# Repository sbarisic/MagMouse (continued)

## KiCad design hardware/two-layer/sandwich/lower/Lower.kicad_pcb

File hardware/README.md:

# Electronics

The [active three-board design](two-layer/sandwich/README.md) uses two copper
layers on each board, passive plastic button clicks and Hall sensing.
Lower and Upper are 70 x 100 mm; Wheel is 70 x 67 mm
with chamfered top corners. All three have independent schematics and routing.

- [Editable projects and reviews](two-layer/sandwich/README.md)
- [Manufacturing quote package](two-layer/sandwich/quote-package/README.md)
- [Combined panel](two-layer/sandwich/panel/Panel.kicad_pcb)
- [3D models](two-layer/sandwich/3d/README.md)
- [Shared libraries and helpers](common/README.md)
- [Historical brake simulation](simulation/brake/README.md)
- [Previous revisions in Git](../docs/history/README.md)

Mechanical integration, supplier acceptance, firmware and physical electronics
qualification remain open. The legacy BOM and circuit/layout notes outside the
active projects contain historical material; use the active schematics and
quote-package BOM for the current fitted components.

License: CERN-OHL-S-2.0; see [LICENSE](LICENSE).
Source location: <https://github.com/sbarisic/MagMouse>.

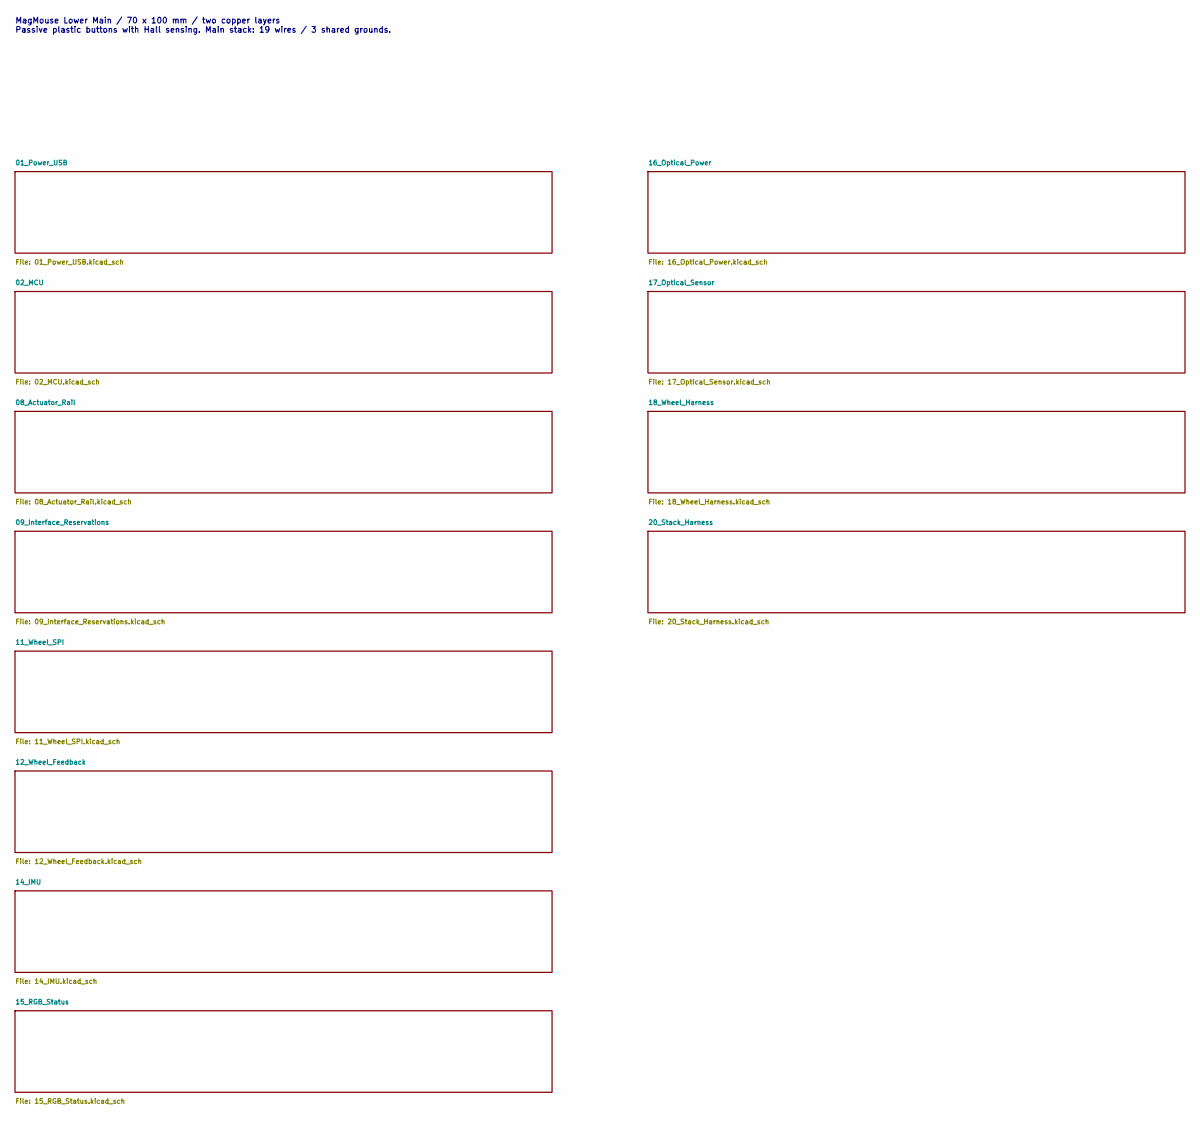
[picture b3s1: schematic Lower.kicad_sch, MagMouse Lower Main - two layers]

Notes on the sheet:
MagMouse Lower Main / 70 x 100 mm / two copper layers Passive plastic buttons with Hall sensing. Main stack: 19 wires / 3 shared grounds.

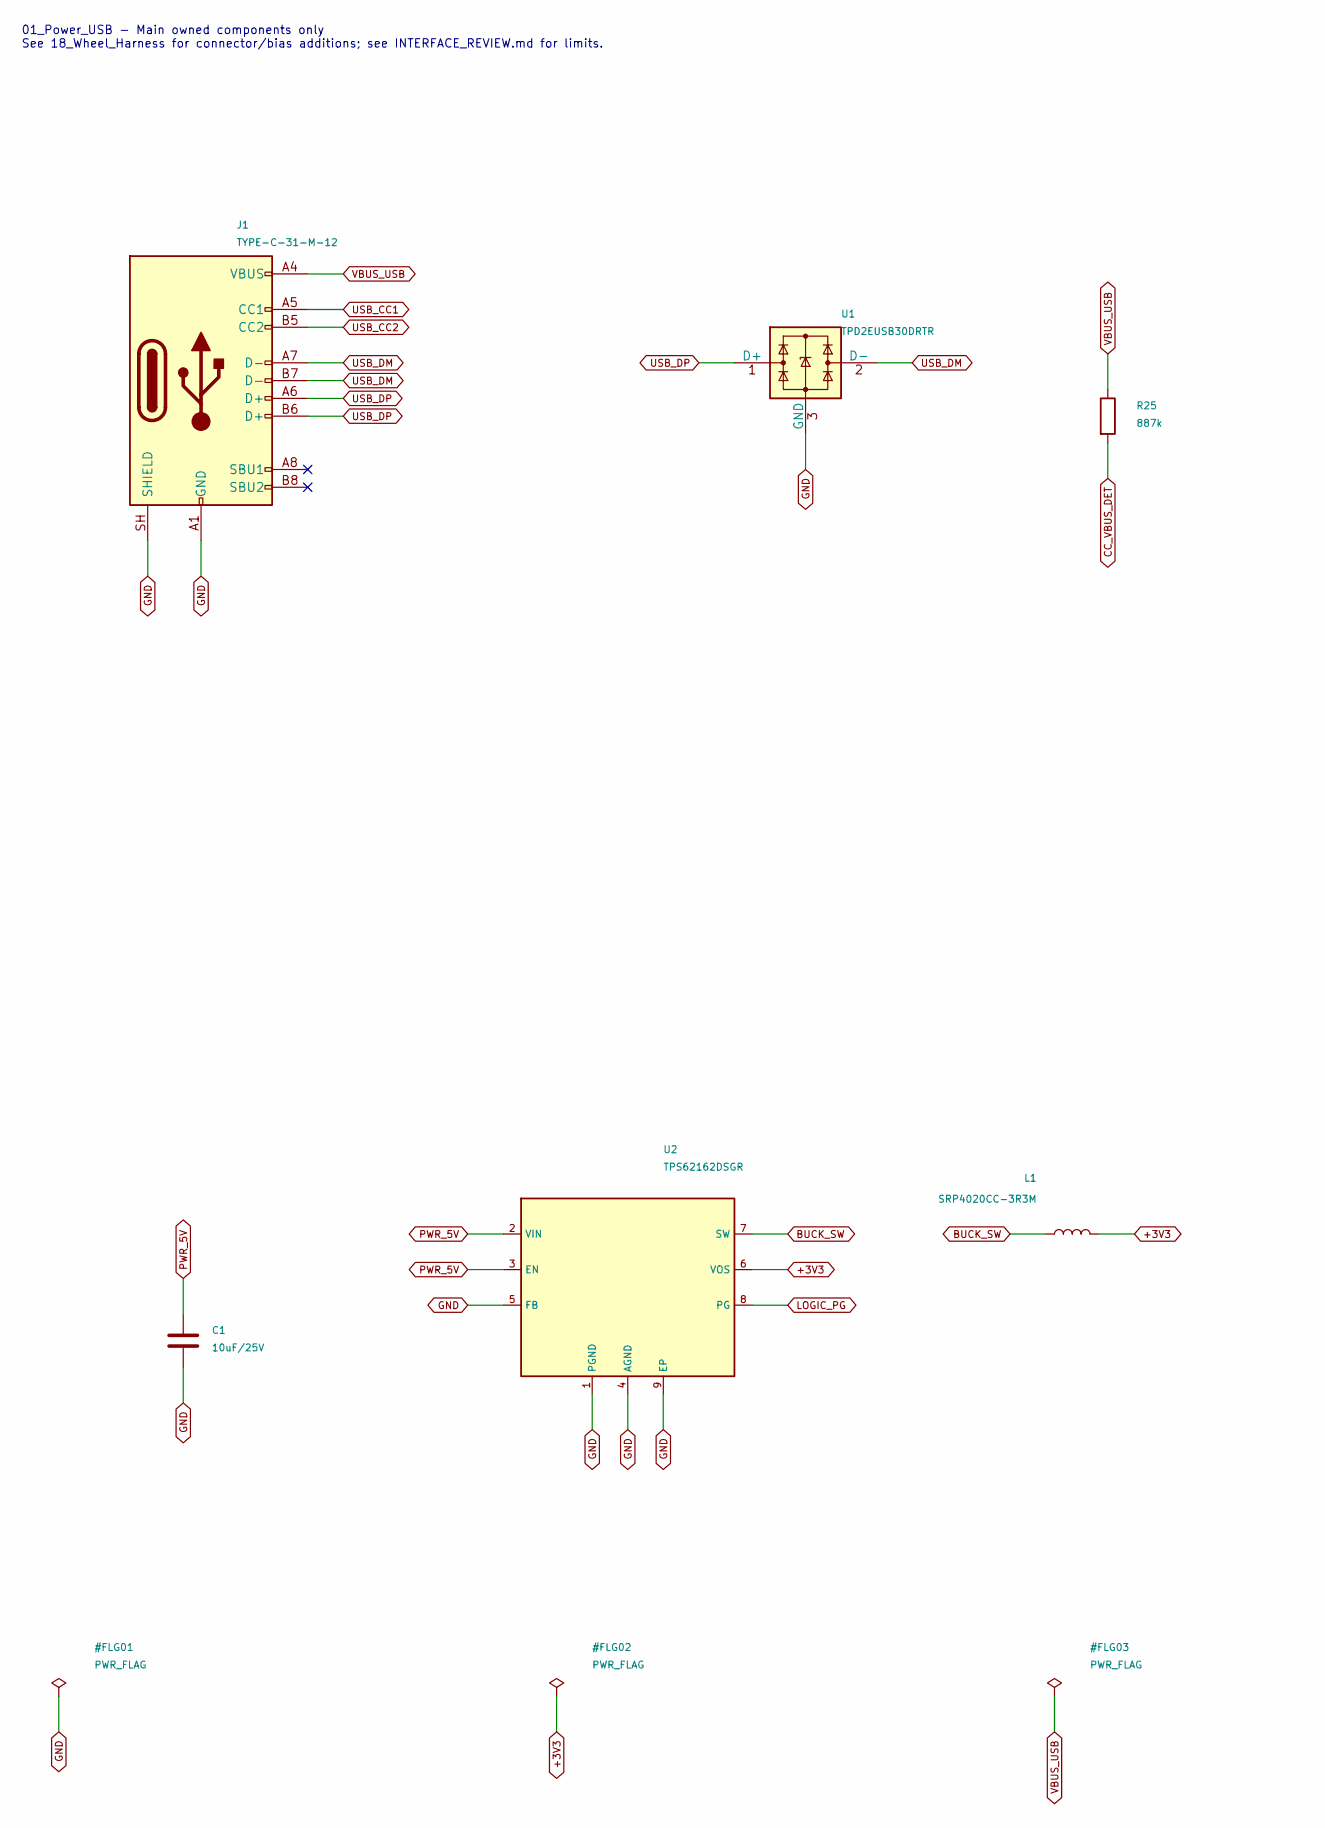
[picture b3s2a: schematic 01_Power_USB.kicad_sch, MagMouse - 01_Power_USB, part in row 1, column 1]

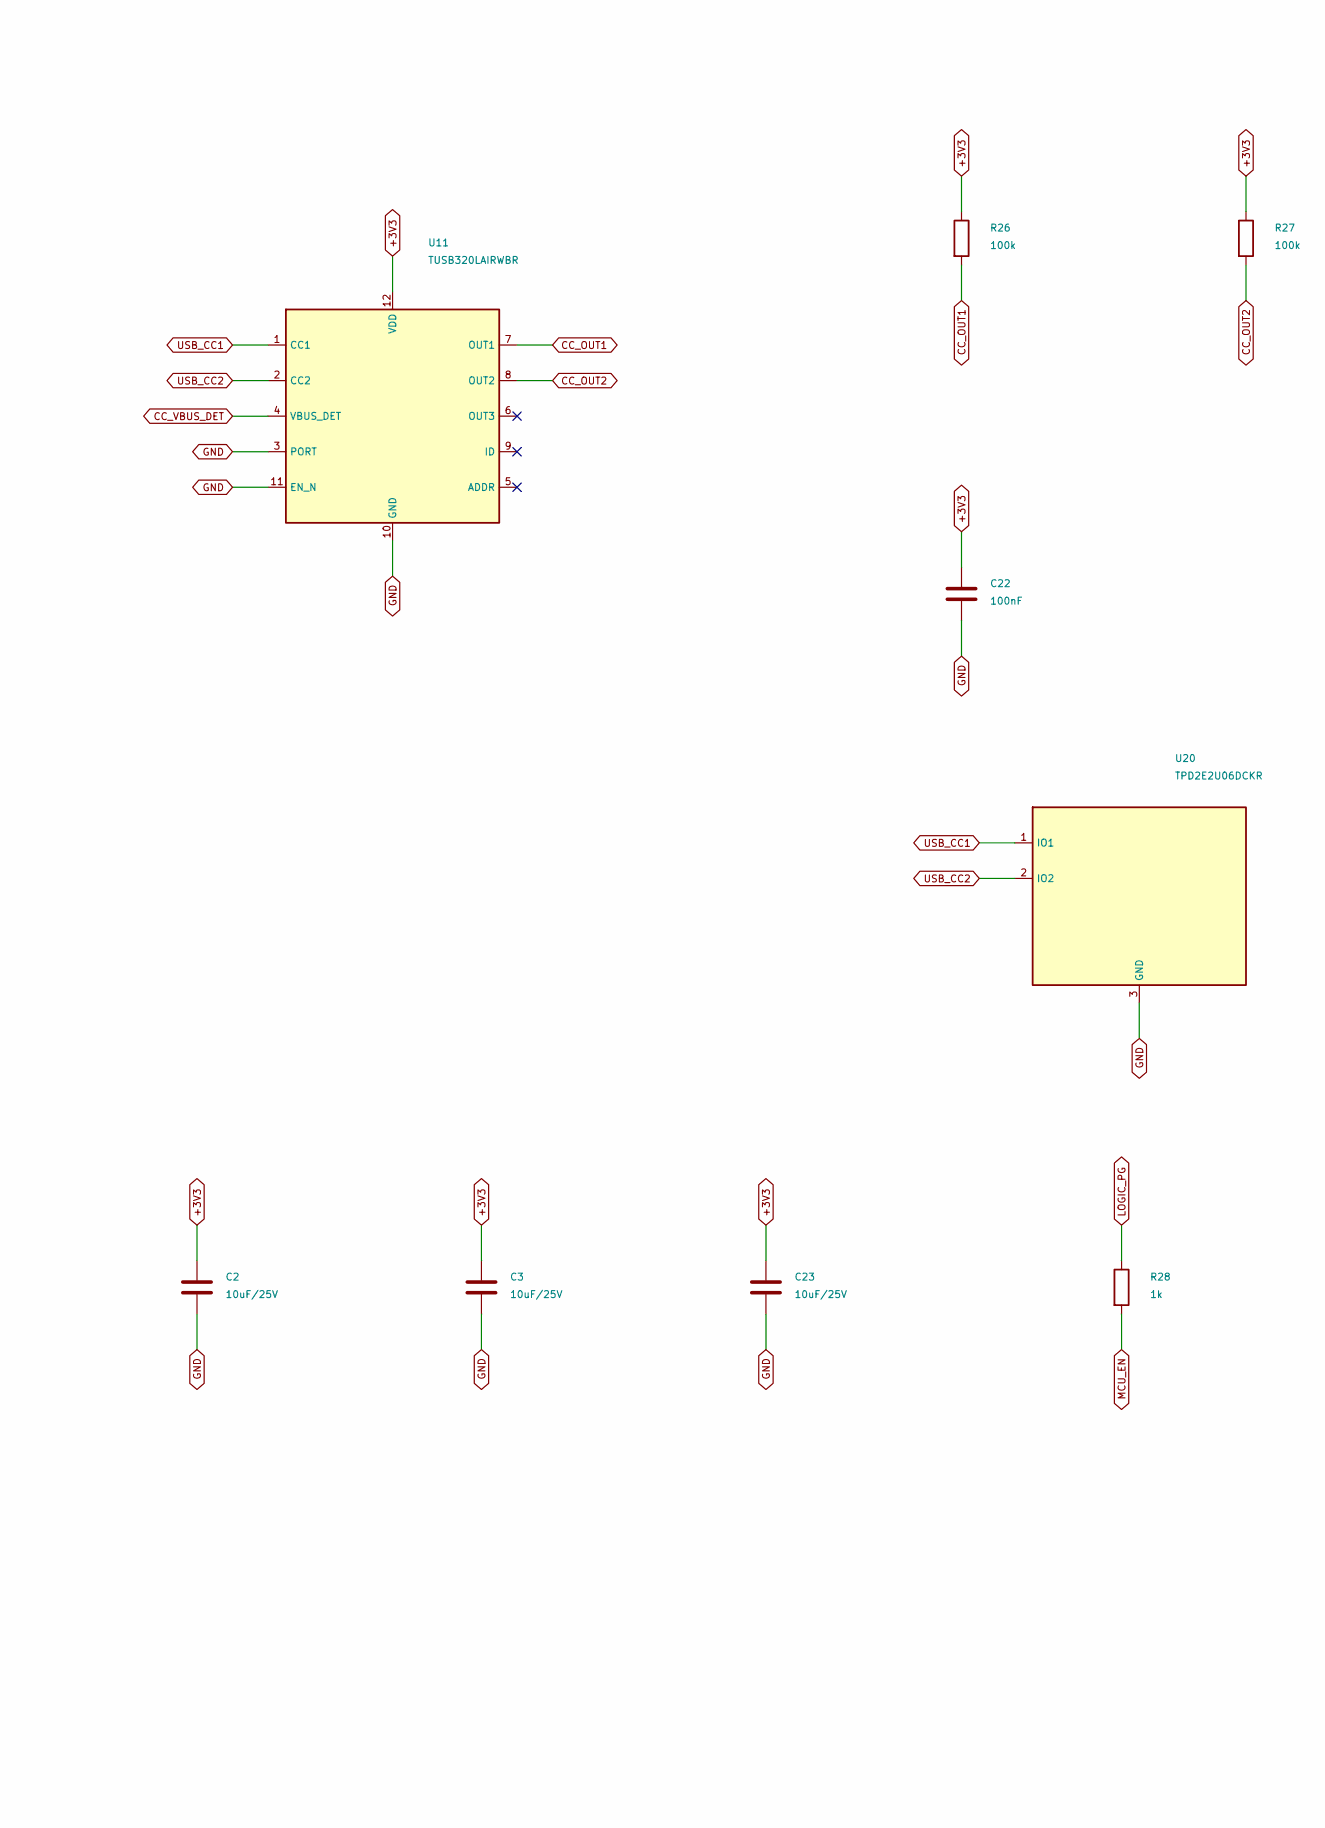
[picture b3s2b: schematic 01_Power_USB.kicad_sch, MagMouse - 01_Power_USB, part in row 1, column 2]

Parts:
C1, C2, C3, C23: 10uF/25V; C_1206_3216Metric; Rating 25 V, X5R, 10%; MPN CL31A106KAHNNNE
C22: 100nF; C_1206_3216Metric; Rating 50 V, X7R, 10%; MPN CC1206KRX7R9BB104
J1: TYPE-C-31-M-12; USB_C_Receptacle_HRO_TYPE-C-31-M-12; MPN TYPE-C-31-M-12; LCSC C165948
L1: SRP4020CC-3R3M; L_Bourns_SRP4020CC; MPN SRP4020CC-3R3M
R25: 887k; R_1206_3216Metric; Rating 0.25 W, 1%; MPN RC1206FR-07887KL
R26, R27: 100k; R_1206_3216Metric; Rating 0.25 W, 1%; MPN RC1206FR-07100KL
R28: 1k; R_1206_3216Metric; Rating 0.25 W, 1%; MPN RC1206FR-071KL
U1: TPD2EUSB30DRTR; Texas_DRT-3; MPN TPD2EUSB30DRTR; LCSC C97502
U2: TPS62162DSGR; Texas_DSG0008A_WSON-8-1EP_2x2mm_P0.5mm_EP0.9x1.6mm; MPN TPS62162DSGR; LCSC C40256
U11: TUSB320LAIRWBR; Texas_X2QFN-12_1.6x1.6mm_P0.4mm; MPN TUSB320LAIRWBR; LCSC C132554
U20: TPD2E2U06DCKR; SOT-323_SC-70; MPN TPD2E2U06DCKR; LCSC C1855726

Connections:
+3V3: C2.1, C3.1, C22.1, C23.1, L1.2, R26.1, R27.1, U2.6 (VOS), U11.12 (VDD); also elsewhere on the board
BUCK_SW: L1.1, U2.7 (SW)
CC_OUT1: R26.2, U11.7 (OUT1); also elsewhere on the board
CC_OUT2: R27.2, U11.8 (OUT2); also elsewhere on the board
CC_VBUS_DET: R25.2, U11.4 (VBUS_DET)
GND: C1.2, C2.2, C3.2, C22.2, C23.2, J1.A1 (GND), J1.A12 (GND), J1.B1 (GND), J1.B12 (GND), J1.SH (SHIELD), U1.3 (GND), U2.1 (PGND), U2.4 (AGND), U2.5 (FB), U2.9 (EP), U11.3 (PORT), U11.10 (GND), U11.11 (EN_N), U20.3 (GND); also elsewhere on the board
LOGIC_PG: R28.1, U2.8 (PG)
MCU_EN: R28.2; also elsewhere on the board
PWR_5V: C1.1, U2.2 (VIN), U2.3 (EN); also elsewhere on the board
USB_CC1: J1.A5 (CC1), U11.1 (CC1), U20.1 (IO1)
USB_CC2: J1.B5 (CC2), U11.2 (CC2), U20.2 (IO2)
USB_DM: J1.A7 (D-), J1.B7 (D-), U1.2 (D-); also elsewhere on the board
USB_DP: J1.A6 (D+), J1.B6 (D+), U1.1 (D+); also elsewhere on the board
VBUS_USB: J1.A4 (VBUS), J1.A9 (VBUS), J1.B4 (VBUS), J1.B9 (VBUS), R25.1; also elsewhere on the board

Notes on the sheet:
01_Power_USB - Main owned components only See 18_Wheel_Harness for connector/bias additions; see INTERFACE_REVIEW.md for limits.

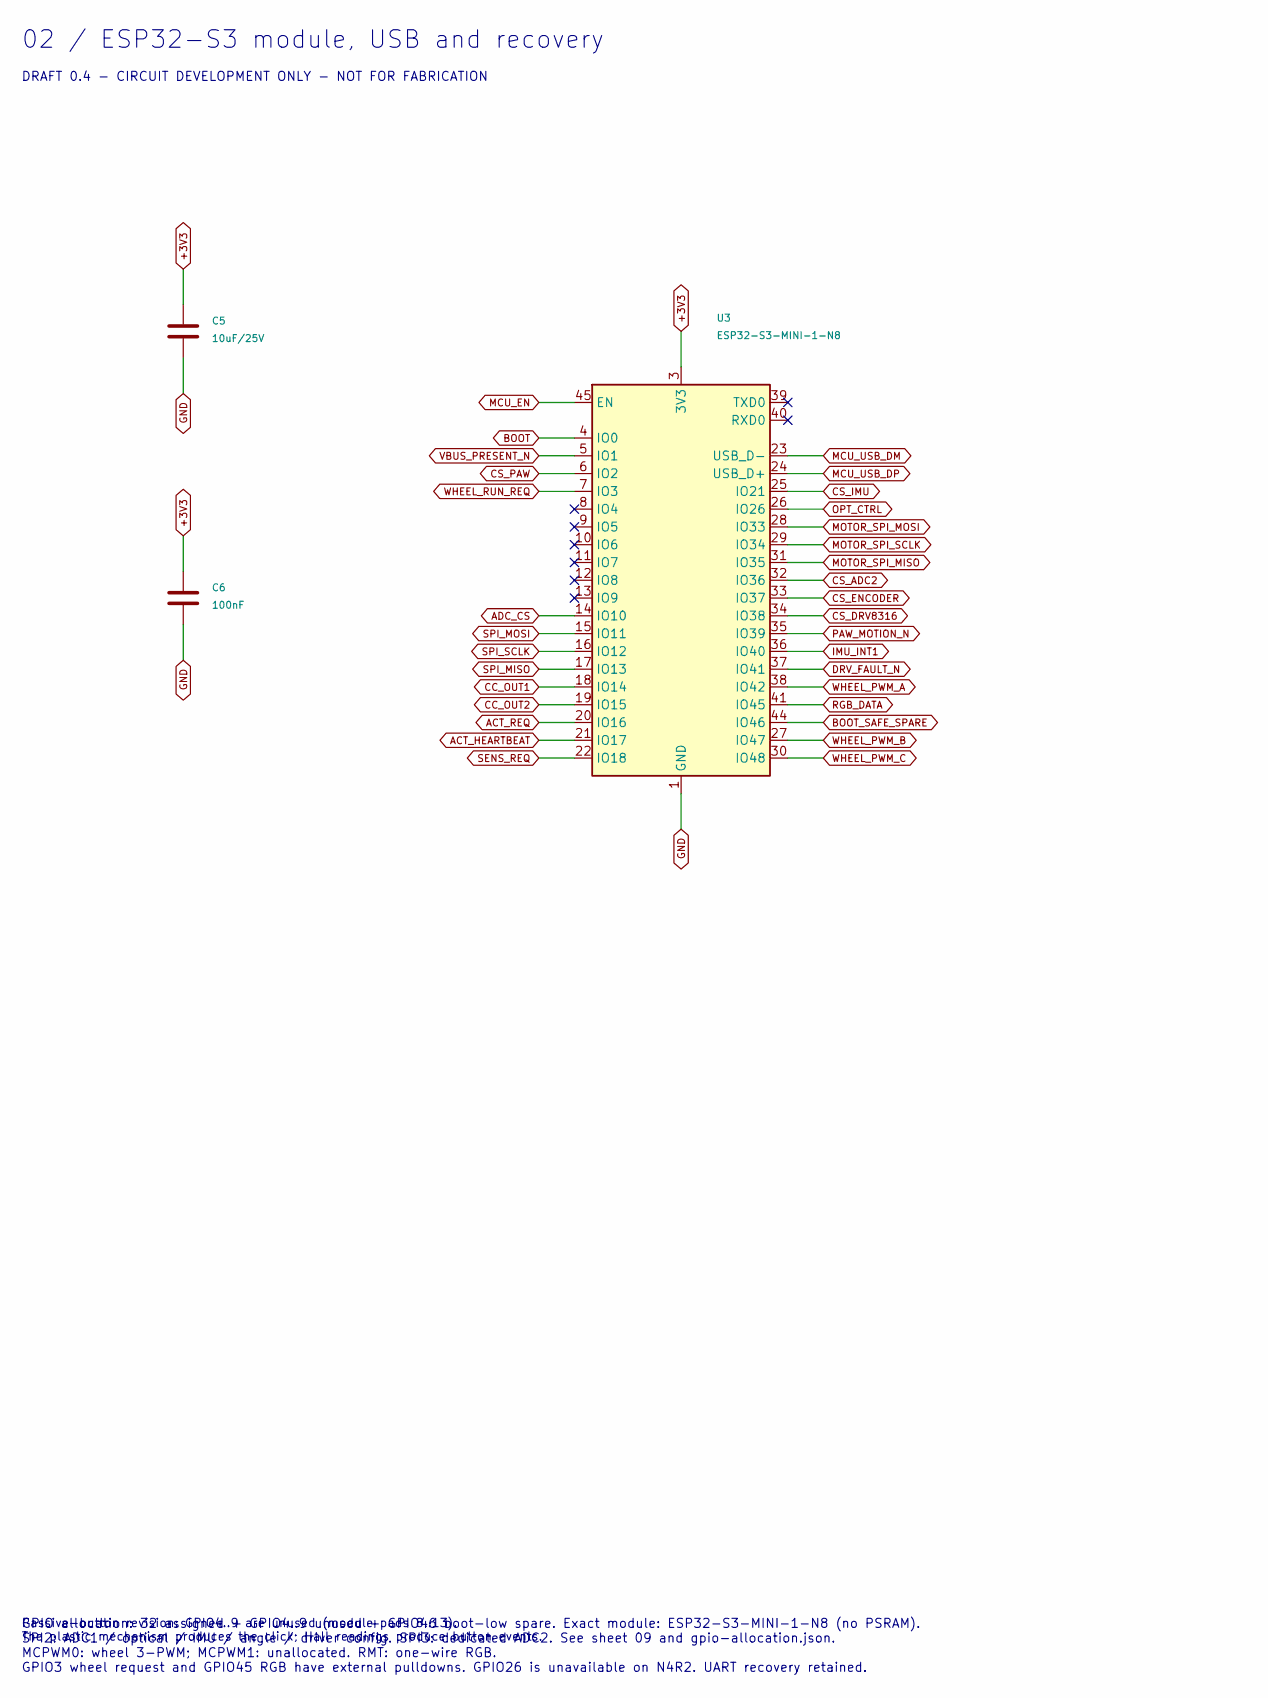
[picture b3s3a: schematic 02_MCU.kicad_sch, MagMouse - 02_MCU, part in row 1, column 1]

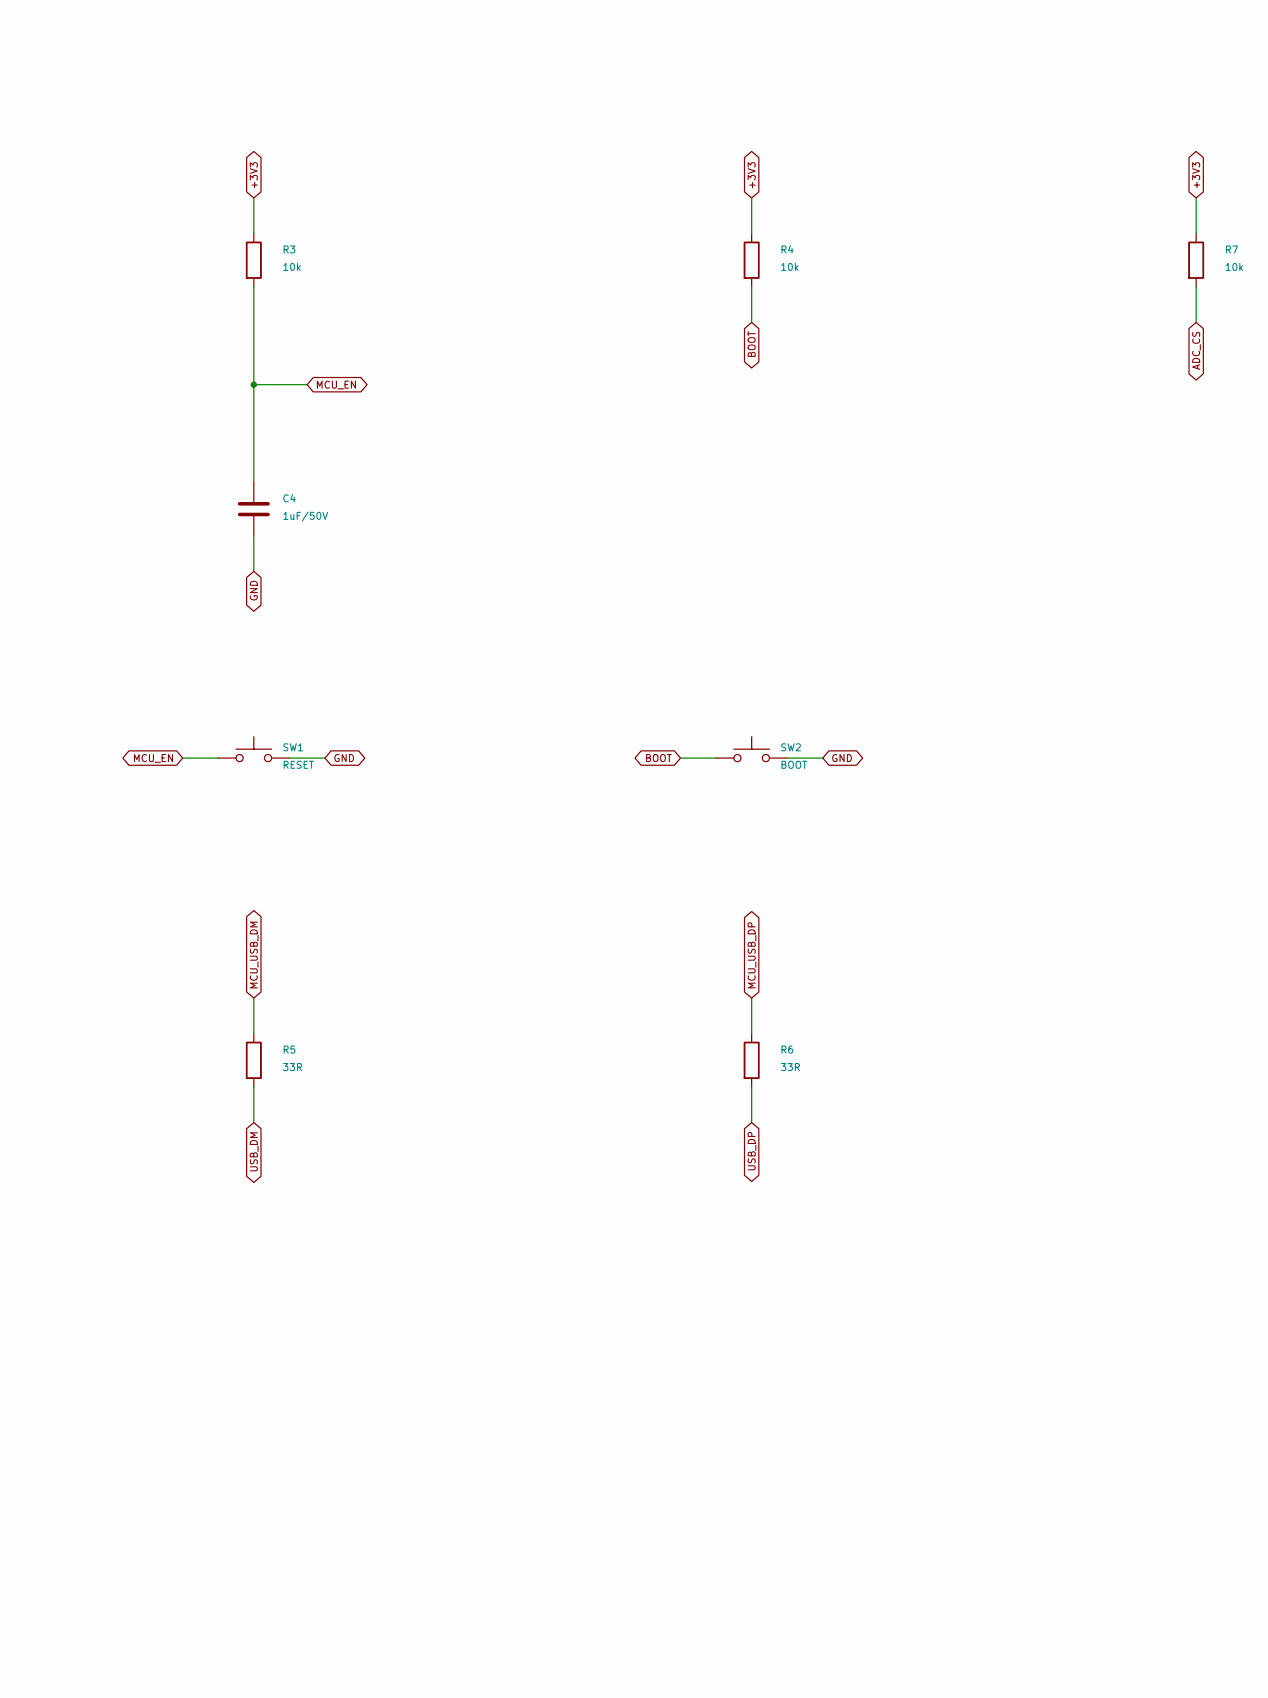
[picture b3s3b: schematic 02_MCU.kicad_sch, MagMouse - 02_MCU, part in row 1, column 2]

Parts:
C4: 1uF/50V; C_1206_3216Metric; Rating 50 V, X7R, 10%; MPN CL31B105KBHNNNE; JLCPCB Library Type Basic
C5: 10uF/25V; C_1206_3216Metric; Rating 25 V, X5R, 10%; MPN CL31A106KAHNNNE
C6: 100nF; C_1206_3216Metric; Rating 50 V, X7R, 10%; MPN CC1206KRX7R9BB104
R3, R4, R7: 10k; R_1206_3216Metric; Rating 0.25 W, 1%; MPN RC1206FR-0710KL
R5, R6: 33R; R_1206_3216Metric; Rating 0.25 W, 1%; MPN RC1206FR-0733RL
SW1: RESET; SW_SPST_TS-1088-xR020; MPN TS-1088-AR02016; LCSC C720477
SW2: BOOT; SW_SPST_TS-1088-xR020; MPN TS-1088-AR02016; LCSC C720477
U3: ESP32-S3-MINI-1-N8; ESP32-S2-MINI-1; MPN ESP32-S3-MINI-1-N8; LCSC C2913206

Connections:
+3V3: C5.1, C6.1, R3.1, R4.1, R7.1, U3.3 (3V3); also elsewhere on the board
ACT_HEARTBEAT: U3.21 (IO17); also elsewhere on the board
ACT_REQ: U3.20 (IO16); also elsewhere on the board
ADC_CS: R7.2, U3.14 (IO10); also elsewhere on the board
BOOT: R4.2, SW2.1, U3.4 (IO0)
BOOT_SAFE_SPARE: U3.44 (IO46); also elsewhere on the board
CC_OUT1: U3.18 (IO14); also elsewhere on the board
CC_OUT2: U3.19 (IO15); also elsewhere on the board
CS_ADC2: U3.32 (IO36); also elsewhere on the board
CS_DRV8316: U3.34 (IO38); also elsewhere on the board
CS_ENCODER: U3.33 (IO37); also elsewhere on the board
CS_IMU: U3.25 (IO21); also elsewhere on the board
CS_PAW: U3.6 (IO2); also elsewhere on the board
DRV_FAULT_N: U3.37 (IO41); also elsewhere on the board
GND: C4.2, C5.2, C6.2, SW1.2, SW2.2, U3.1 (GND), U3.2 (GND), U3.42 (GND), U3.43 (GND), U3.46 (GND), U3.47 (GND), U3.48 (GND), U3.49 (GND), U3.50 (GND), U3.51 (GND), U3.52 (GND), U3.53 (GND), U3.54 (GND), U3.55 (GND), U3.56 (GND), U3.57 (GND), U3.58 (GND), U3.59 (GND), U3.60 (GND), U3.61 (GND), U3.62 (GND), U3.63 (GND), U3.64 (GND), U3.65 (GND); also elsewhere on the board
IMU_INT1: U3.36 (IO40); also elsewhere on the board
MCU_EN: C4.1, R3.2, SW1.1, U3.45 (EN); also elsewhere on the board
MCU_USB_DM: R5.1, U3.23 (USB_D-)
MCU_USB_DP: R6.1, U3.24 (USB_D+)
MOTOR_SPI_MISO: U3.31 (IO35); also elsewhere on the board
MOTOR_SPI_MOSI: U3.28 (IO33); also elsewhere on the board
MOTOR_SPI_SCLK: U3.29 (IO34); also elsewhere on the board
OPT_CTRL: U3.26 (IO26); also elsewhere on the board
PAW_MOTION_N: U3.35 (IO39); also elsewhere on the board
RGB_DATA: U3.41 (IO45); also elsewhere on the board
SENS_REQ: U3.22 (IO18); also elsewhere on the board
SPI_MISO: U3.17 (IO13); also elsewhere on the board
SPI_MOSI: U3.15 (IO11); also elsewhere on the board
SPI_SCLK: U3.16 (IO12); also elsewhere on the board
USB_DM: R5.2; also elsewhere on the board
USB_DP: R6.2; also elsewhere on the board
VBUS_PRESENT_N: U3.5 (IO1); also elsewhere on the board
WHEEL_PWM_A: U3.38 (IO42); also elsewhere on the board
WHEEL_PWM_B: U3.27 (IO47); also elsewhere on the board
WHEEL_PWM_C: U3.30 (IO48); also elsewhere on the board
WHEEL_RUN_REQ: U3.7 (IO3); also elsewhere on the board

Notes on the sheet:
02 / ESP32-S3 module, USB and recovery
DRAFT 0.4 - CIRCUIT DEVELOPMENT ONLY - NOT FOR FABRICATION
GPIO allocation: 32 assigned + GPIO4..9 unused + GPIO46 boot-low spare. Exact module: ESP32-S3-MINI-1-N8 (no PSRAM). SPI2: ADC1 / optical / IMU / angle / driver config. SPI3: dedicated ADC2. See sheet 09 and gpio-allocation.json. MCPWM0: wheel 3-PWM; MCPWM1: unallocated. RMT: one-wire RGB. GPIO3 wh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
Passive-button revision: GPIO4..9 are unused (module pads 8..13). The plastic mechanism produces the click; Hall readings produce button events.

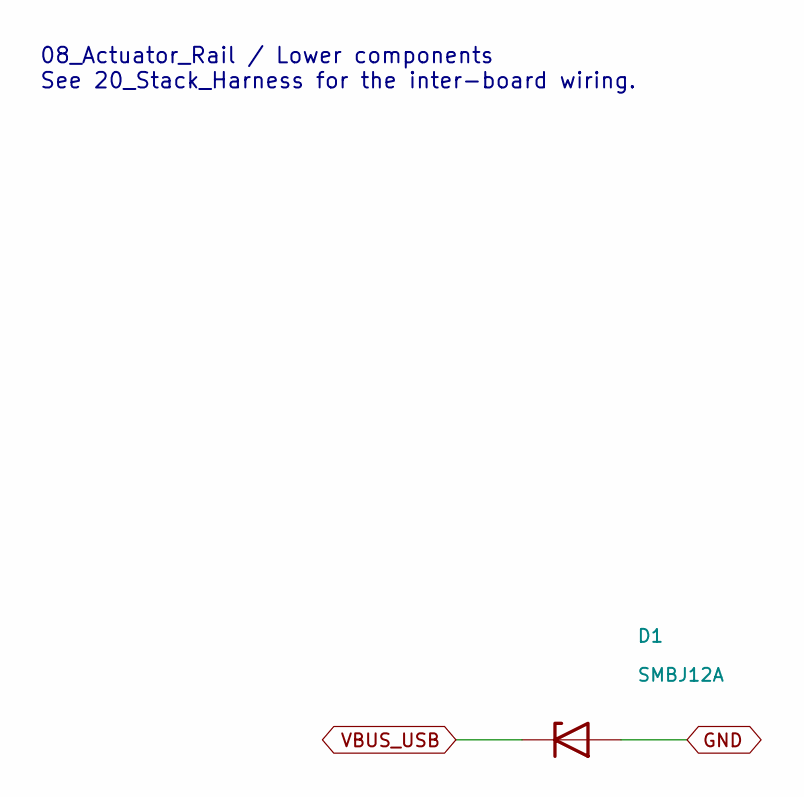
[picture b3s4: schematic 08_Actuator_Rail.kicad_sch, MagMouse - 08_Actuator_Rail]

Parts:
D1: SMBJ12A; D_SMB; MPN SMBJ12A; LCSC C151251

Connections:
GND: D1.2 (A); also elsewhere on the board
VBUS_USB: D1.1 (K); also elsewhere on the board

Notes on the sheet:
08_Actuator_Rail / Lower components See 20_Stack_Harness for the inter-board wiring.

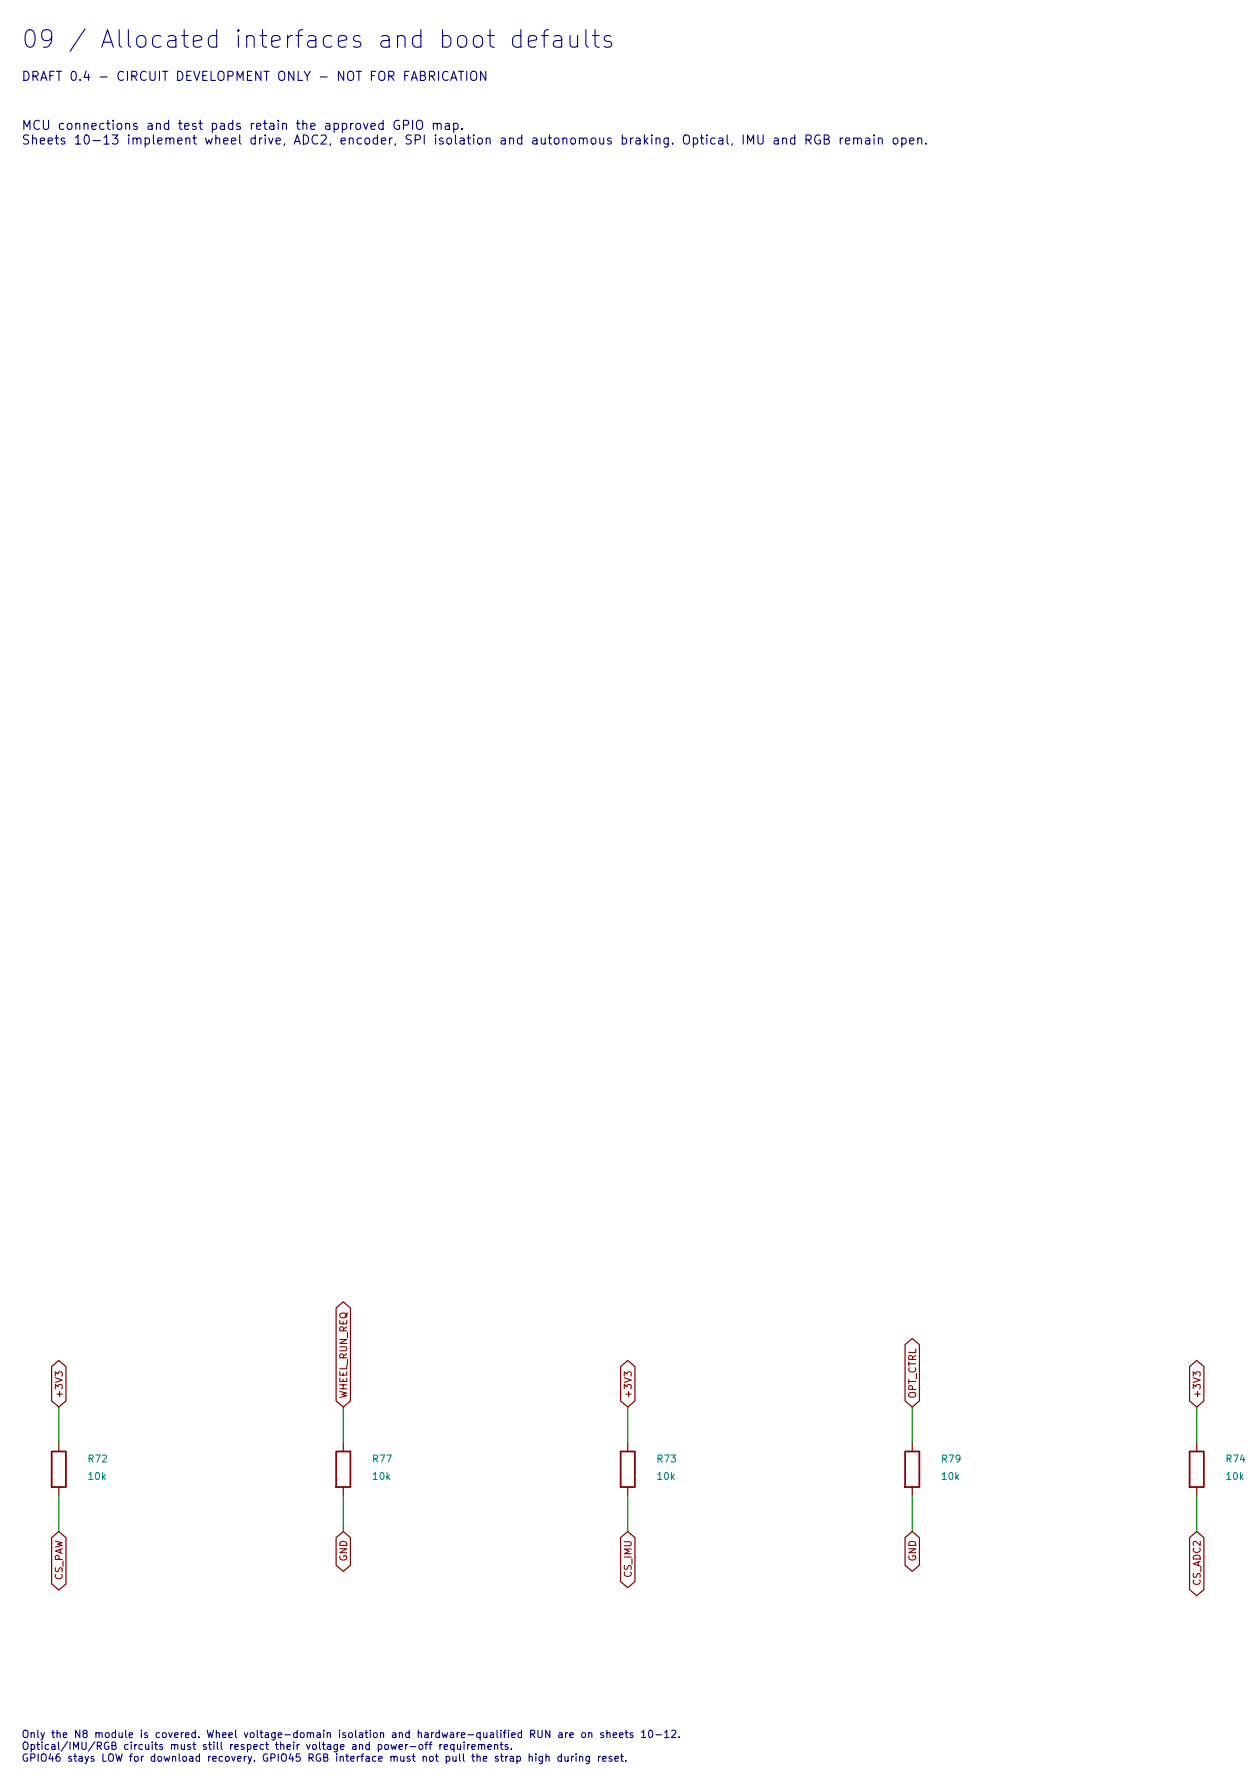
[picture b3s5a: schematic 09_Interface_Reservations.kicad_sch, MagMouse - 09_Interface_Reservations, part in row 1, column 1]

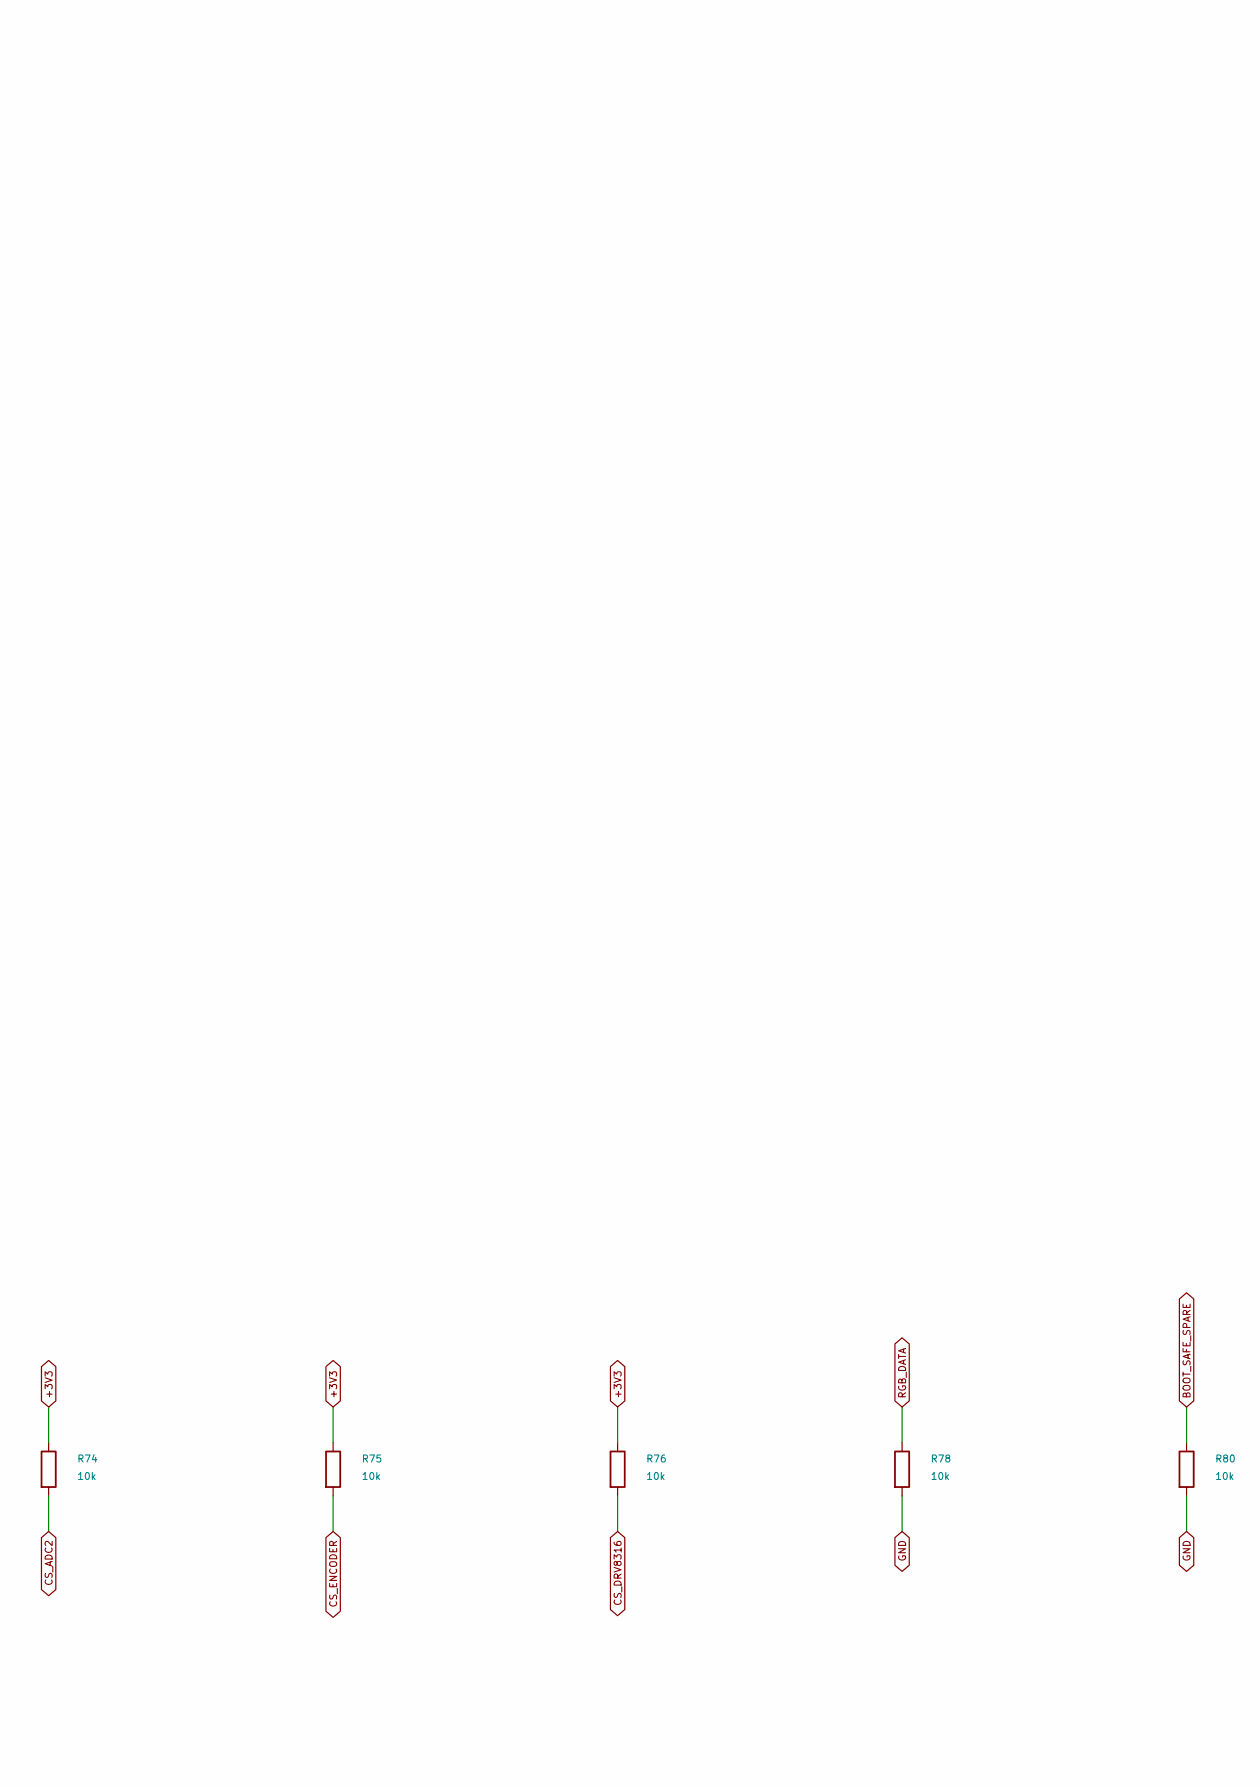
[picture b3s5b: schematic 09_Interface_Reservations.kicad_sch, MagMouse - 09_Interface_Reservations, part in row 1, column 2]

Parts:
R72, R73, R74, R75, R76, R77, R78, R79, R80: 10k; R_1206_3216Metric; Rating 0.25 W, 1%; MPN RC1206FR-0710KL

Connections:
+3V3: R72.1, R73.1, R74.1, R75.1, R76.1; also elsewhere on the board
BOOT_SAFE_SPARE: R80.1; also elsewhere on the board
CS_ADC2: R74.2; also elsewhere on the board
CS_DRV8316: R76.2; also elsewhere on the board
CS_ENCODER: R75.2; also elsewhere on the board
CS_IMU: R73.2; also elsewhere on the board
CS_PAW: R72.2; also elsewhere on the board
GND: R77.2, R78.2, R79.2, R80.2; also elsewhere on the board
OPT_CTRL: R79.1; also elsewhere on the board
RGB_DATA: R78.1; also elsewhere on the board
WHEEL_RUN_REQ: R77.1; also elsewhere on the board

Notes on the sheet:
09 / Allocated interfaces and boot defaults
DRAFT 0.4 - CIRCUIT DEVELOPMENT ONLY - NOT FOR FABRICATION
MCU connections and test pads retain the approved GPIO map. Sheets 10-13 implement wheel drive, ADC2, encoder, SPI isolation and autonomous braking. Optical, IMU and RGB remain open.
Only the N8 module is covered. Wheel voltage-domain isolation and hardware-qualified RUN are on sheets 10-12. Optical/IMU/RGB circuits must still respect their voltage and power-off requirements. GPIO46 stays LOW for download recovery. GPIO45 RGB interface must not pull the strap high during reset.
